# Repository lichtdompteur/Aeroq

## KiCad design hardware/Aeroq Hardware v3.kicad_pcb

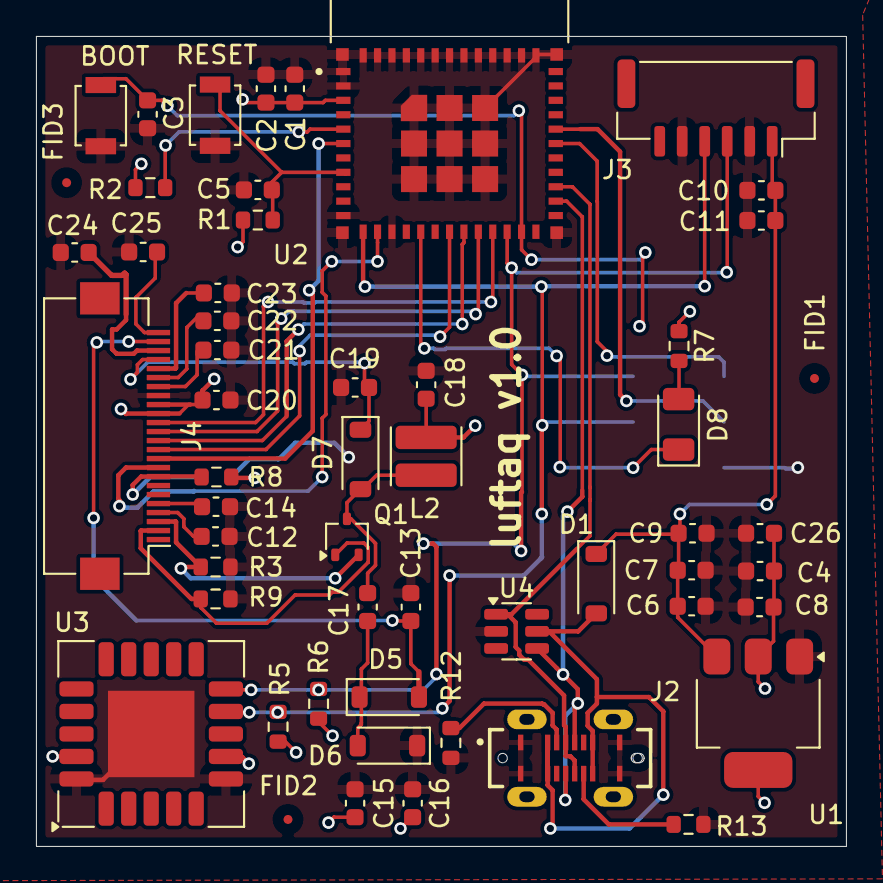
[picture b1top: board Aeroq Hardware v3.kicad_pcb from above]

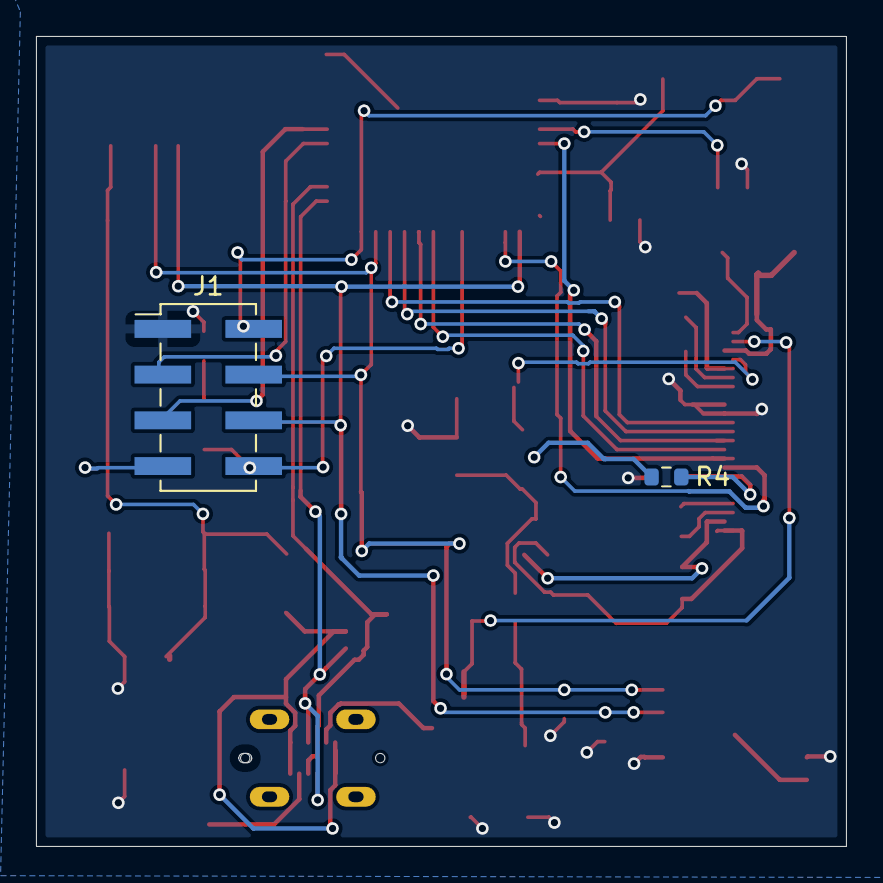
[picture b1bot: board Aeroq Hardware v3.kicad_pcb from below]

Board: 2 copper layers, 45.0 x 45.0 mm, 57 parts (2 on the bottom side), 37 nets.

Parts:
C1, C4, C6, C9, C10, C12, C13, C14, C16, C17, C18, C19, C23, C24, C26: 4.7uF_0603_25V; C_0603_1608Metric
C2, C3, C5, C7, C8, C11, C15: 100nF_0603_16V; C_0603_1608Metric
C20, C21, C22, C25: 1uF_0603_25V; C_0603_1608Metric
D1, D5, D6, D7: MBR0530; D_SOD-123
D8: Green LED; LED_1206_3216Metric
FID1, FID2, FID3: Fiducial; Fiducial_0.5mm_Mask1.5mm
J1: 2x4 male header 2.54 mm; PinHeader_2x04_P2.54mm_Vertical_SMD
J2: USB4120-03-C; GCT_USB4120-03-C_REVA
J3: SM06B-GHS-TB; JST_GH_SM06B-GHS-TB_1x06-1MP_P1.25mm_Horizontal
J4: FH12A-24S-0.5SH(55); Hirose_FH12-24S-0.5SH_1x24-1MP_P0.50mm_Horizontal_INVERTED
L2: 10 uH; L_Wuerth_MAPI-3020
Q1: Si1308EDL; SOT-323_SC-70
R1, R2, R5, R6, R8, R9: 10k_0603; R_0603_1608Metric
R3: 0.47R_0603; R_0603_1608Metric
R4: 3Ω_0603; R_0603_1608Metric
R7: 2.2k_0603; R_0603_1608Metric
R12, R13: 5.1k_0603; R_0603_1608Metric
S1, S2: B3U-1000P; SW_SPST_B3U-1000P
U1: TLV76133DCY; SOT-223-3_TabPin2
U2: ESP32-C3-MINI-1-N4; XCVR_ESP32-C3-MINI-1-N4
U3: SCD40-D-R2; Sensirion_SCD4x-1EP_10.1x10.1mm_P1.25mm_EP4.8x4.8mm
U4: USBLC6-2SC6; SOT-23-6

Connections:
+3.3V: C1.1, C2.1, C4.2, C8.1, C15.1, C16.2, C18.1, C20.2, C26.2, J1.1, J4.15, J4.16, L2.1, R1.2, R2.2, R5.2, R6.2, R7.1, R8.2, U1.2 (VO), U2.3 (3V3), U3.7 (VDD), U3.19 (VDD)
+5V: C6.2, C7.1, C9.2, C10.2, C11.1, D1.1 (K), J3.1, U1.3 (VI)
/Display/BUSY: J4.9, U2.13 (IO1)
/Display/CS: J4.12, U2.19 (IO5)
/Display/D/C: J4.11, U2.18 (IO4)
/Display/GDR: J4.2, Q1.1 (G), R9.2
/Display/PREVGH: C19.1, D7.1 (K), J4.21
/Display/PREVGL: C13.1, D5.2 (A), J4.23
/Display/RES: J4.10, U2.6 (IO3)
/Display/RESE: J4.3, Q1.2 (S), R3.1
/Display/SCLK: J4.13, U2.20 (IO6)
/Display/SDI: J4.14, U2.21 (IO7)
/Microcontroller/CHIP_PU: C5.1, R1.1, S2.2, U2.8 (EN)
/Microcontroller/GPIO9: C3.1, J1.2, S1.2, U2.23 (IO9)
/Microcontroller/GPIO10: D8.1 (K), J1.8, U2.16 (IO10)
/Microcontroller/RXD: J1.3, U2.30 (RXD0)
/Microcontroller/SCL: J1.6, J3.4, R5.1, U2.12 (IO0), U3.9 (SCL)
/Microcontroller/SDA: J1.4, J3.3, R6.1, U2.22 (IO8), U3.10 (SDA)
/Microcontroller/TXD: J1.5, U2.31 (TXD0)
/USB-C/D+: J2.A6 (D1+), J2.B6 (D2+), U2.27 (IO19), U4.1 (I/O1)
/USB-C/D-: J2.A7 (D1-), J2.B7 (D2-), U2.26 (IO18), U4.4 (I/O2)
GND: C1.2, C2.2, C3.2, C4.1, C5.2, C6.1, C7.2, C8.2, C9.1, C10.1, C11.2, C12.1, C13.2, C14.1, C15.2, C16.1, C18.2, C19.2, C20.1, C21.2, C22.2, C23.1, C24.1, C25.1, C26.1, D6.1 (K), J1.7, J2.A1 (GND_A), J2.A12 (GND_A), J2.B1 (GND_B), J2.B12 (GND_B), J3.2, J3.5, J4.17, R3.2, R4.1, R9.1, R12.2, R13.2, S1.1, S2.1, U1.1 (GND), U2.1 (GND), U2.2 (GND), U2.11 (GND), U2.14 (GND), U2.36 (GND), U2.37 (GND), U2.38 (GND), U2.39 (GND), U2.40 (GND), U2.41 (GND), U2.42 (GND), U2.43 (GND), U2.44 (GND), U2.45 (GND), U2.46 (GND), U2.47 (GND), U2.48 (GND), U2.49_1 (GND), U2.49_2 (GND), U2.49_3 (GND), U2.49_4 (GND), U2.49_5 (GND), U2.49_6 (GND), U2.49_7 (GND), U2.49_8 (GND), U2.49_9 (GND), U2.50 (GND), U2.51 (GND), U2.52 (GND), U2.53 (GND), U3.6 (GND), U3.20 (GND), U3.21 (GND), U4.2 (GND)
unnamed: C17.1, D5.1 (K), D6.2 (A)
unnamed: C17.2, D7.2 (A), L2.2, Q1.3 (D)
unnamed: D8.2 (A), R7.2
unnamed: J2.A5 (CC1), R12.1
unnamed: J2.B5 (CC2), R13.1
unnamed: C12.2, J4.4
unnamed: C14.2, J4.5
unnamed: J4.8, R4.2, R8.1
unnamed: C21.1, J4.18
unnamed: C22.1, J4.19
unnamed: C23.2, J4.20
unnamed: C24.2, J4.22
unnamed: C25.2, J4.24
unnamed: R2.1, U2.5 (IO2)
VBUS: D1.2 (A), J2.A4 (VBUS_A), J2.A9 (VBUS_A), J2.B4 (VBUS_B), J2.B9 (VBUS_B), U4.5 (VBUS)

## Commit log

2025-10-16 add kibot workflow
2025-10-16 fix workflow
2025-10-16 fix ERC
2025-10-16 remove diff feature
2025-10-16 fix whitespace in MPN
